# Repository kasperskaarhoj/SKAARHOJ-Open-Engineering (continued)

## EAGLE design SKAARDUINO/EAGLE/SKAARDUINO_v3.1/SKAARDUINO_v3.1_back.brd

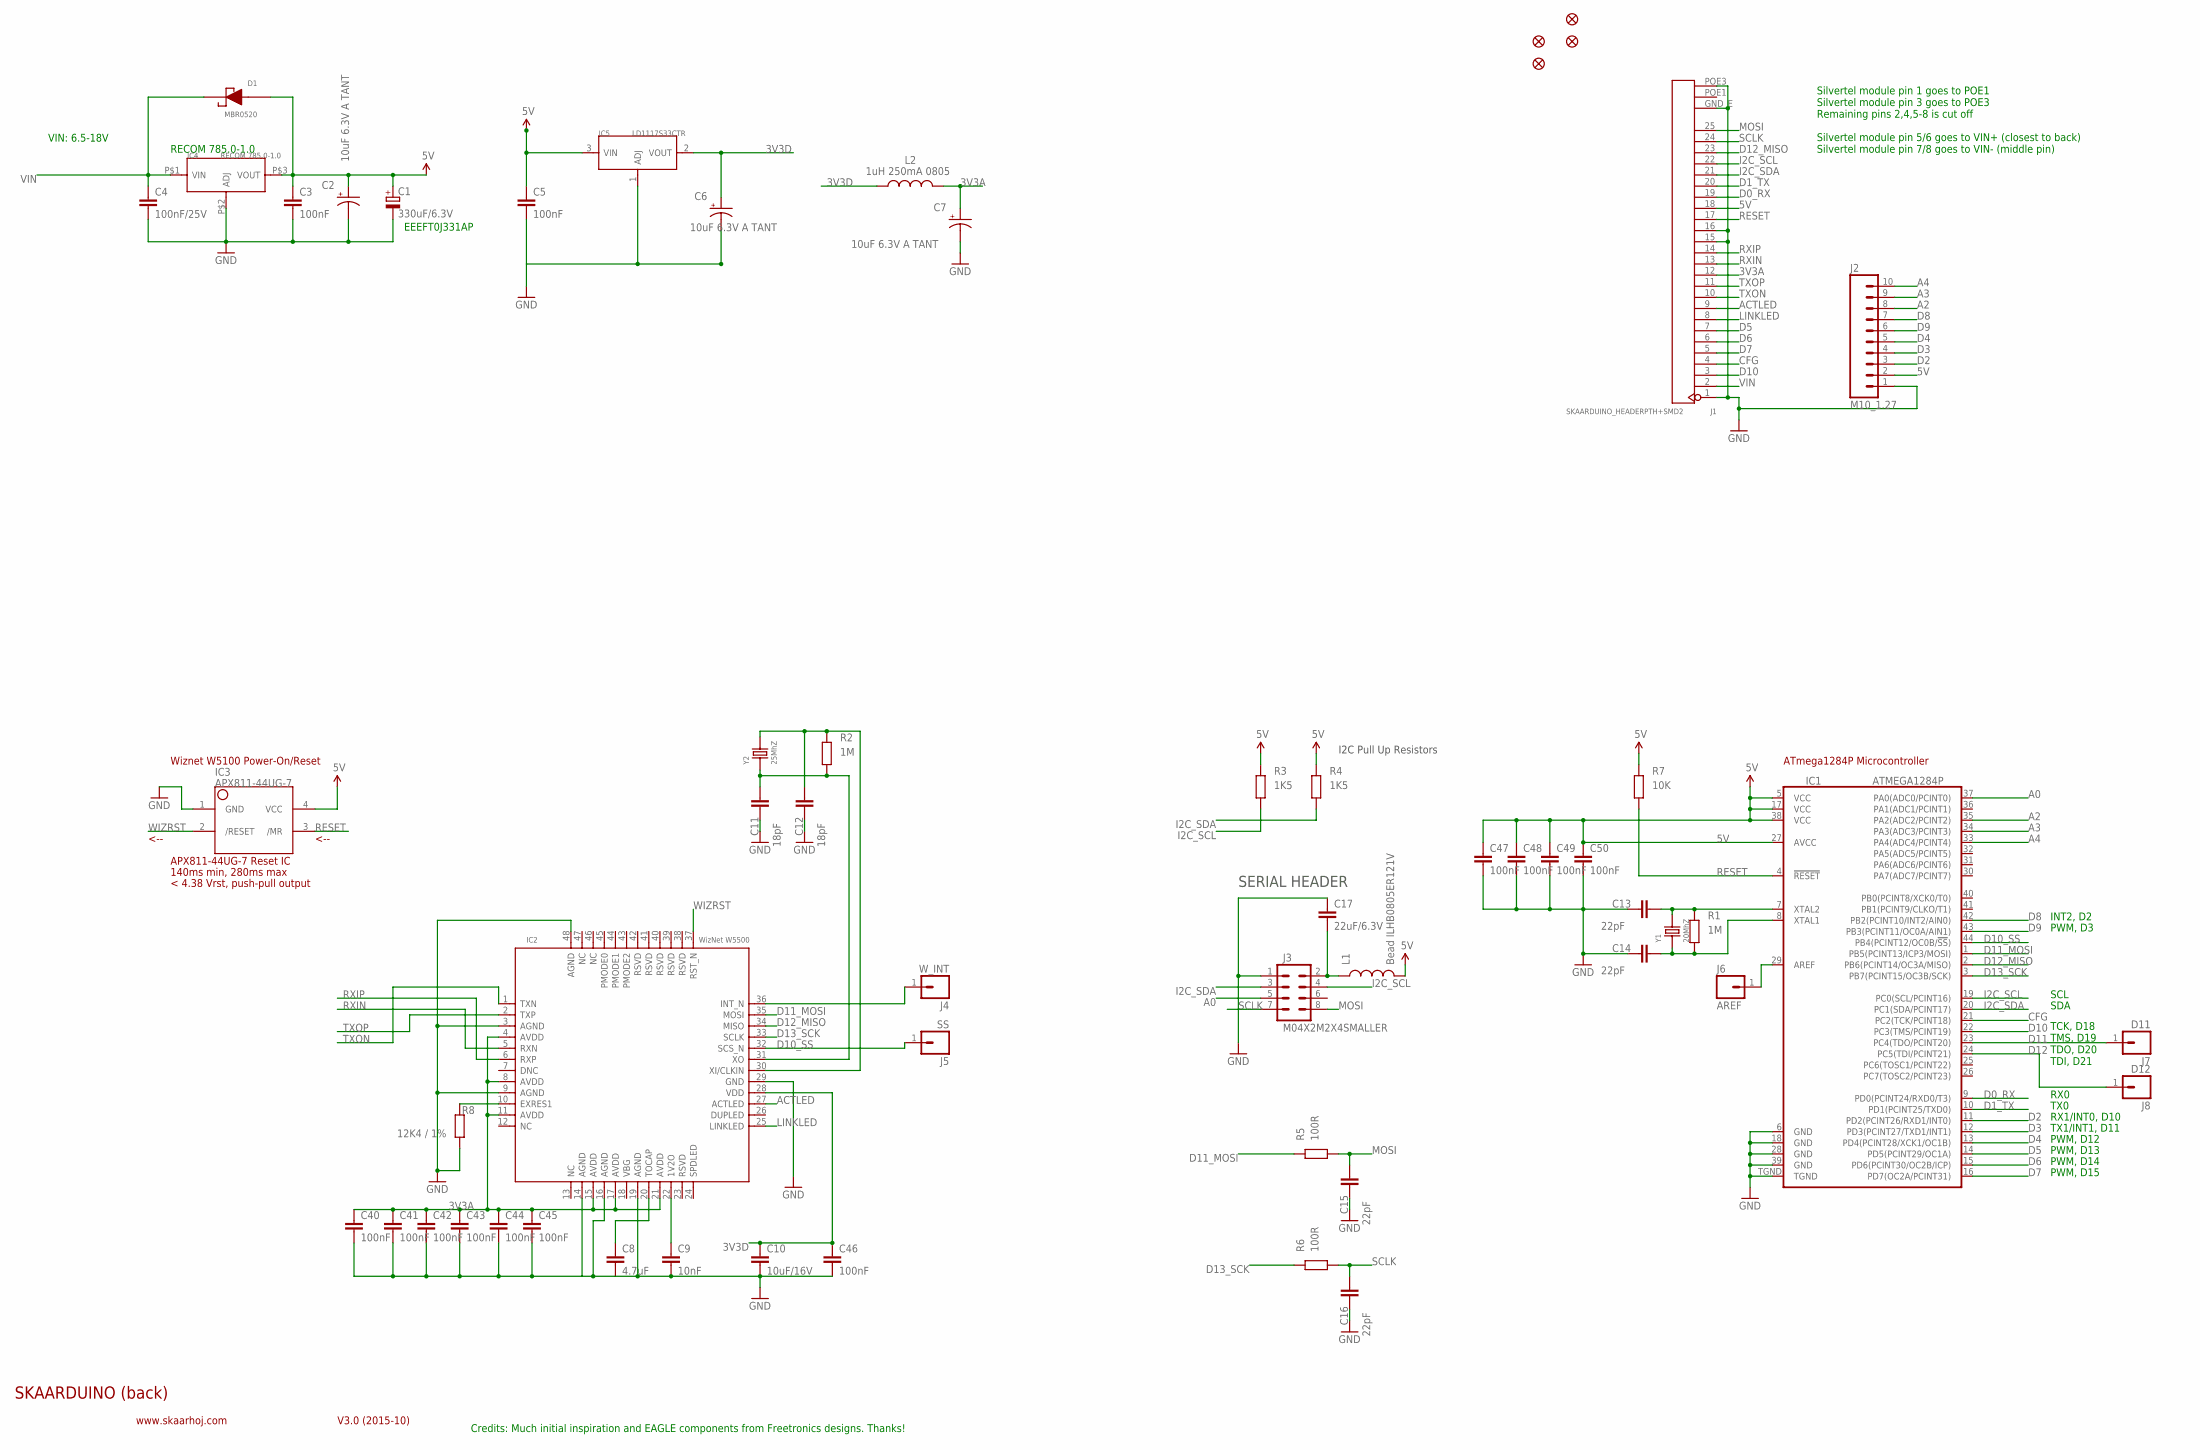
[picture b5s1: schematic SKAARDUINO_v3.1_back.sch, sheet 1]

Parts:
C1: 330uF/6.3V; PANASONIC_D
C2, C6, C7: 10uF 6.3V A TANT; EIA3216
C3, C5, C40, C41, C42, C43, C44, C45, C46, C47, C48, C49, C50: 100nF; 0402C
C4: 100nF/25V; 0402C
C8: 4.7uF; 0805
C9: 10nF; 0402C
C10: 10uF/16V; 0805
C11, C12: 18pF; 0402C
C13, C14, C15, C16: 22pF; 0402C
C17: 22uF/6.3V; 0805
D1: MBR0520; SOD-123
FID1, FID2, FID3, FID4: FIDUCIAL1X2.5; FIDUCIAL-1X2.5
IC1: ATMEGA1284P; QFN-44M1
IC2: WizNet W5500; LQFP-48
IC3: APX811-44UG-7; SOT143-R
IC4: RECOM 785.0-1.0; RECOM_785.0-1.0
IC5: LD1117S33CTR; SOT-223-UPRIGHT
J1: SKAARDUINO_HEADERPTH+SMD2; SKAARDUINO_PTH_SMD2_HEADER
J2: M10_1.27; M10X1
J3: M04X2M2X4SMALLER; M2X4SMALLER
J4: W_INT; M1X1
J5: SS; M1X1
J6: AREF; M1X1
J7: D11; M1X1
J8: D12; M1X1
L1: Bead ILHB0805ER121V; 0805
L2: 1uH 250mA 0805; L2012C
R1, R2: 1M; 0402
R3, R4: 1K5; 0402
R5, R6: 100R; 0402
R7: 10K; 0402
R8: 12K4 / 1%; 0402
Y1: 20MhZ; X2-SMD-5.0X3.2X1.3MM
Y2: 25MhZ; X2-SMD-5.0X3.2X1.3MM

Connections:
3V3A: C7.A (+), C40.1, C41.1, C42.1, C43.1, C44.1, C45.1, IC2.4 (AVDD), IC2.8 (AVDD), IC2.11 (AVDD), IC2.15 (AVDD), IC2.17 (AVDD), IC2.21 (AVDD), J1.12, L2.2
3V3D: C6.A (+), C10.1, C46.1, IC2.28 (VDD), IC5.2 (VOUT), L2.1
5V: C1.+, C2.A (+), C3.1, C5.1, C47.1, C48.1, C49.1, C50.1, D1.2 (AN), IC1.5 (VCC), IC1.17 (VCC), IC1.27 (AVCC), IC1.38 (VCC), IC3.4 (VCC), IC4.P$3 (VOUT), IC5.3 (VIN), J1.18, J2.2, L1.2, R3.2, R4.2, R7.2
A0: IC1.37 (PA0(ADC0/PCINT0)), J3.5
A2: IC1.35 (PA2(ADC2/PCINT2)), J2.8
A3: IC1.34 (PA3(ADC3/PCINT3)), J2.9
A4: IC1.33 (PA4(ADC4/PCINT4)), J2.10
ACTLED: IC2.27 (ACTLED), J1.9
CFG: IC1.21 (PC2(TCK/PCINT18)), J1.4
D0_RX: IC1.9 (PD0(PCINT24/RXD0/T3)), J1.19
D1_TX: IC1.10 (PD1(PCINT25/TXD0)), J1.20
D2: IC1.11 (PD2(PCINT26/RXD1/INT0)), J2.3
D3: IC1.12 (PD3(PCINT27/TXD1/INT1)), J2.4
D4: IC1.13 (PD4(PCINT28/XCK1/OC1B)), J2.5
D5: IC1.14 (PD5(PCINT29/OC1A)), J1.7
D6: IC1.15 (PD6(PCINT30/OC2B/ICP)), J1.6
D7: IC1.16 (PD7(OC2A/PCINT31)), J1.5
D8: IC1.42 (PB2(PCINT10/INT2/AIN0)), J2.7
D9: IC1.43 (PB3(PCINT11/OC0A/AIN1)), J2.6
D10: IC1.22 (PC3(TMS/PCINT19)), J1.3
D10_SS: IC1.44 (PB4(PCINT12/OC0B/!SS!)), IC2.32 (SCS_N), J5.1
D11: IC1.23 (PC4(TDO/PCINT20)), J7.1
D11_MOSI: IC1.1 (PB5(PCINT13/ICP3/MOSI)), IC2.35 (MOSI), R5.2
D12: IC1.24 (PC5(TDI/PCINT21)), J8.1
D12_MISO: IC1.2 (PB6(PCINT14/OC3A/MISO)), IC2.34 (MISO), J1.23
D13_SCK: IC1.3 (PB7(PCINT15/OC3B/SCK)), IC2.33 (SCLK), R6.2
GND: C1.-, C2.C (-), C3.2, C4.2, C5.2, C6.C (-), C7.C (-), C8.2, C9.2, C10.2, C11.1, C12.1, C13.1, C14.1, C15.1, C16.1, C17.1, C40.2, C41.2, C42.2, C43.2, C44.2, C45.2, C46.2, C47.2, C48.2, C49.2, C50.2, IC1.6 (GND), IC1.18 (GND), IC1.28 (GND), IC1.39 (GND), IC1.TGND, IC2.3 (AGND), IC2.9 (AGND), IC2.14 (AGND), IC2.16 (AGND), IC2.19 (AGND), IC2.29 (GND), IC2.48 (AGND), IC3.1 (GND), IC4.P$2 (ADJ), IC5.1 (ADJ), J1.1, J1.15, J1.16, J1.GND_E (26), J1.POE3 (28), J2.1, J3.1, R8.1
I2C_SCL: IC1.19 (PC0(SCL/PCINT16)), J1.22, J3.4, R3.1
I2C_SDA: IC1.20 (PC1(SDA/PCINT17)), J1.21, J3.3, R4.1
LINKLED: IC2.25 (LINKLED), J1.8
MOSI: C15.2, J1.25, J3.8, R5.1
unnamed: C17.2, J3.2, L1.1
unnamed: IC2.36 (INT_N), J4.1
unnamed: C14.2, IC1.8 (XTAL1), R1.1, Y1.1
unnamed: C13.2, IC1.7 (XTAL2), R1.2, Y1.2
unnamed: IC1.29 (AREF), J6.1
unnamed: C8.1, IC2.20 (TOCAP)
unnamed: C9.1, IC2.22 (1V2O)
unnamed: IC2.10 (EXRES1), R8.2
RESET: IC1.4 (!RESET), IC3.3 (/MR), J1.17, R7.1
RXIN: IC2.5 (RXN), J1.13
RXIP: IC2.6 (RXP), J1.14
SCLK: C16.2, J1.24, J3.7, R6.1
TXON: IC2.1 (TXN), J1.10
TXOP: IC2.2 (TXP), J1.11
VIN: C4.1, D1.1 (CA), IC4.P$1 (VIN), J1.2
WIZRST: IC2.37 (RST_N), IC3.2 (/RESET)
XTLN: C12.2, IC2.30 (XI/CLKIN), R2.2, Y2.2
XTLP: C11.2, IC2.31 (XO), R2.1, Y2.1

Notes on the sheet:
APX811-44UG-7 Reset IC
140ms min, 280ms max
Wiznet W5100 Power-On/Reset
SKAARDUINO (back)
V3.0 (2015-10)
www.skaarhoj.com
< 4.38 Vrst, push-pull output
<--
ATmega1284P Microcontroller
I2C Pull Up Resistors
SERIAL HEADER
Credits: Much initial inspiration and EAGLE components from Freetronics designs. Thanks!
EEEFT0J331AP
RECOM 785.0-1.0
VIN: 6.5-18V
PWM, D3
PWM, D12
PWM, D13
PWM, D14
PWM, D15
RX1/INT0, D10
TX1/INT1, D11
INT2, D2
TX0
RX0
SCL
SDA
TCK, D18 TMS, D19 TDO, D20 TDI, D21
Silvertel module pin 1 goes to POE1 Silvertel module pin 3 goes to POE3 Remaining pins 2,4,5-8 is cut off Silvertel module pin 5/6 goes to VIN+ (closest to back) Silvertel module pin 7/8 goes to VIN- (middle pin)

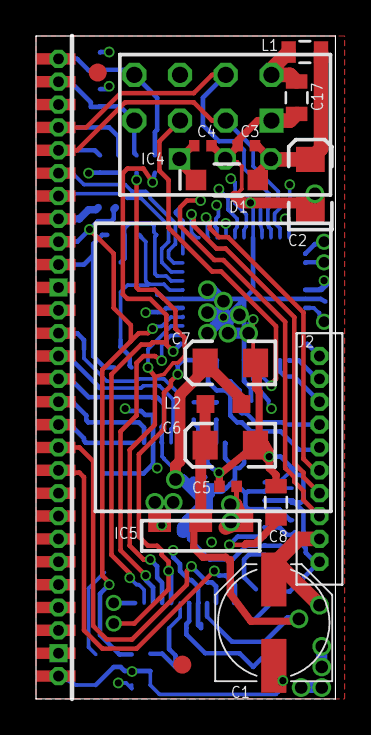
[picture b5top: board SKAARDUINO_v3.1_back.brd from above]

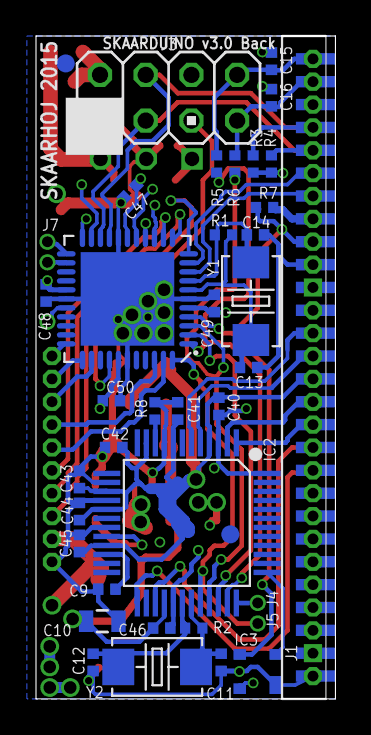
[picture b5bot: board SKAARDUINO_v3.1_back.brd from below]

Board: 4 copper layers, 16.6 x 36.8 mm, 58 parts (37 on the bottom side), 49 nets.
